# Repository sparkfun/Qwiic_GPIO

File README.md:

SparkFun Qwiic GPIO
=======================================

[*SparkFun Qwiic GPIO (DEV-17047)*](https://www.sparkfun.com/products/17047)

TCA9534 breakout board with Qwiic connectors and easy-to-use latch terminals; no longer screw wires into place! Use this board to add more GPIO pins to your system.

Repository Contents
-------------------

* **/Documents** - Contains datasheets and schematic.pdf
* **/Hardware** - Current .brd and .sch files for product
* **/Production** - Production panel files (.brd)

License Information
-------------------

This product is _**open source**_!

Please review the LICENSE.md file for license information.

If you have any questions or concerns on licensing, please contact technical support on our [SparkFun forums](https://forum.sparkfun.com/viewforum.php?f=152).

Distributed as-is; no warranty is given.

- Your friends at SparkFun._

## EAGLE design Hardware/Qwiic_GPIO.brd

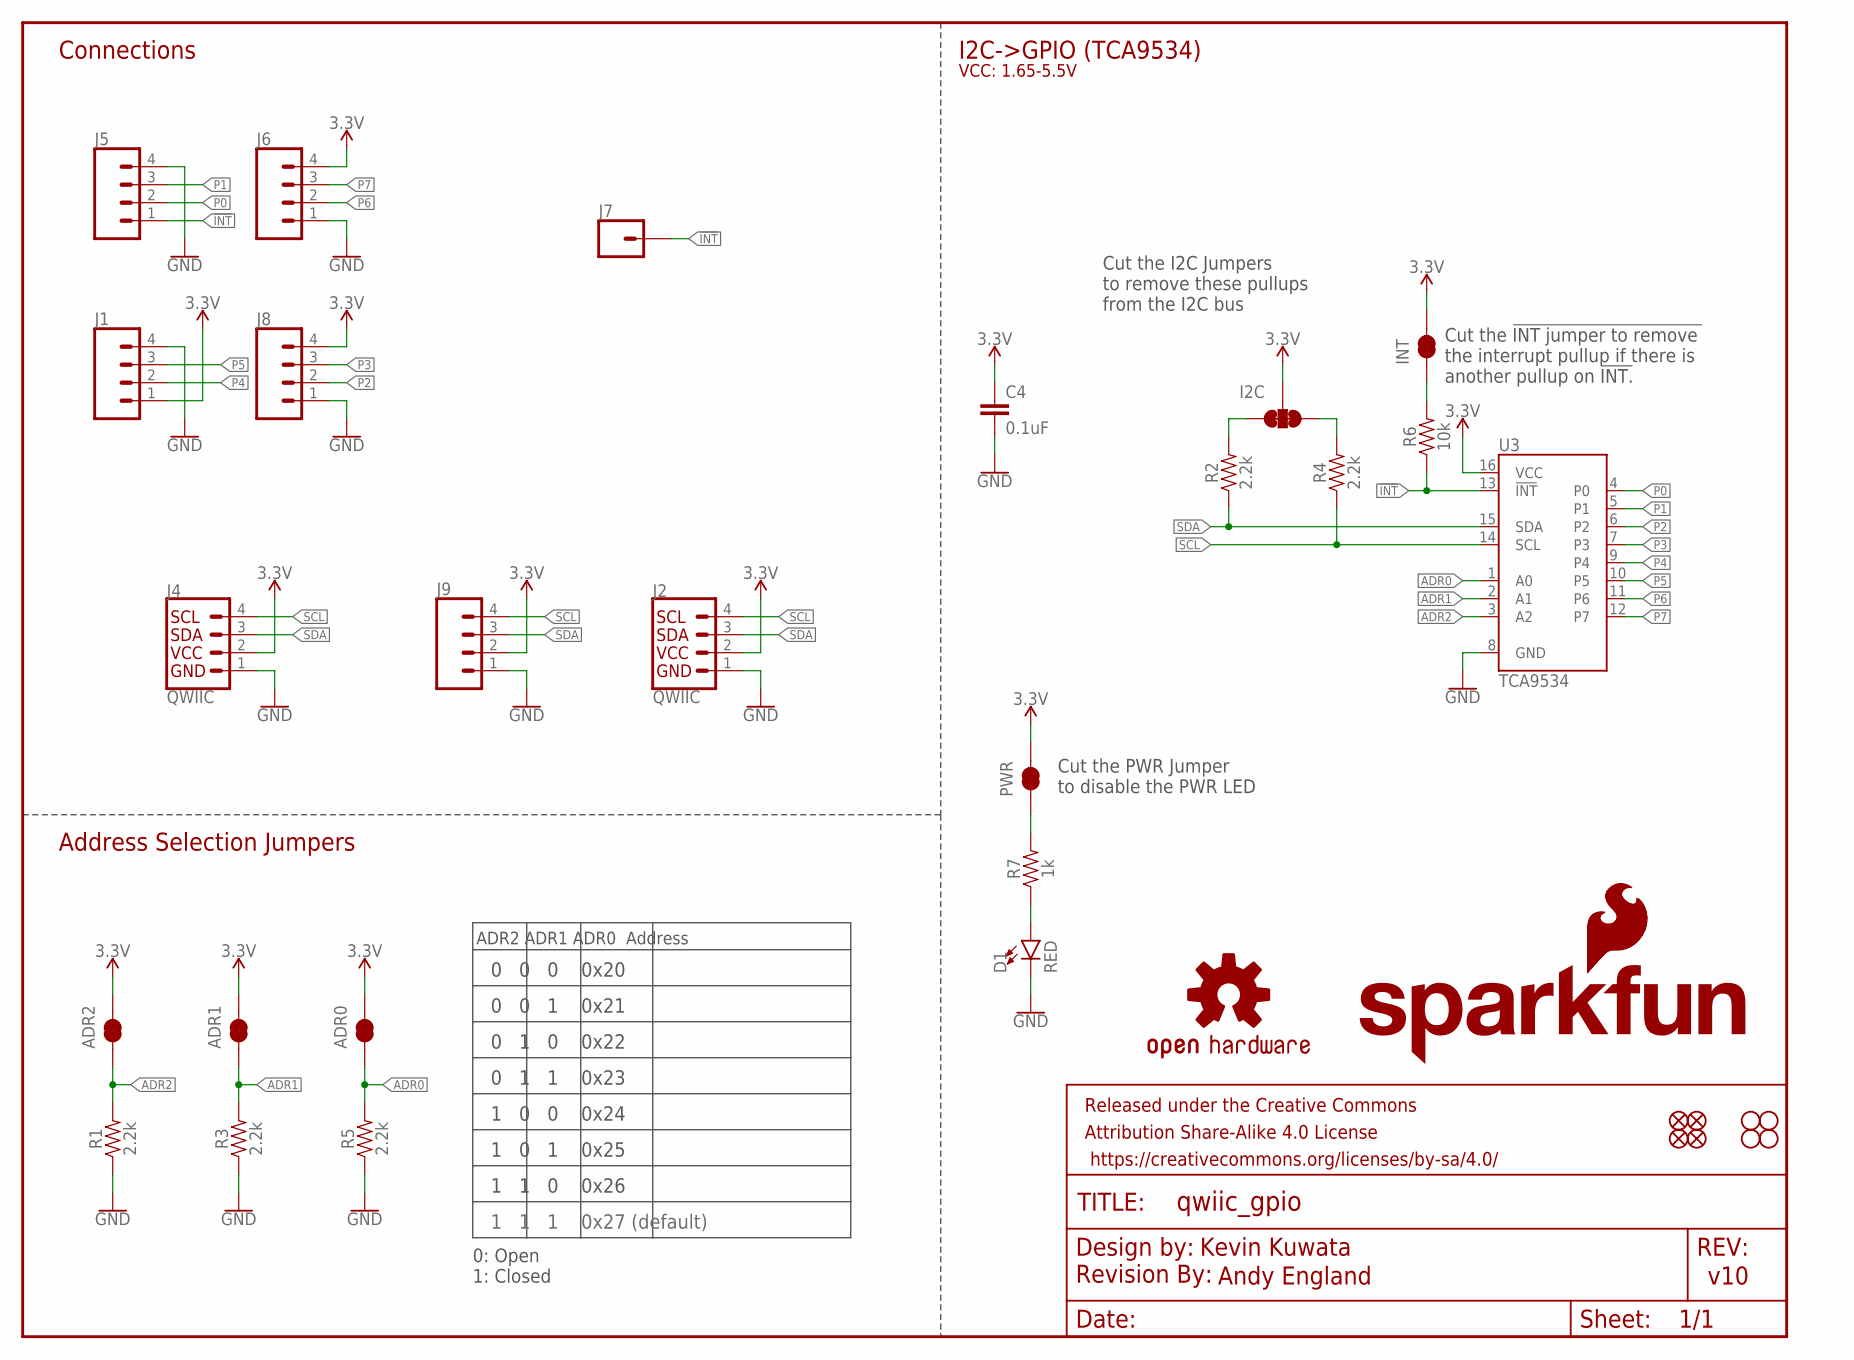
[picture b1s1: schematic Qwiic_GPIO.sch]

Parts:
ADR0, ADR1, ADR2: JUMPER-SMT_2_NC_TRACE_SILK; SMT-JUMPER_2_NC_TRACE_SILK
C4: 0.1uF; 0603
D1: RED; LED-0603
FD1, FD2: FIDUCIAL1X2; FIDUCIAL-1X2
FRAME1: FRAME-LETTER; CREATIVE_COMMONS
H1, H2: STAND-OFF
I2C: JUMPER-SMT_3_2-NC_TRACE_SILK; SMT-JUMPER_3_2-NC_TRACE_SILK
INT: JUMPER-SMT_2_NC_TRACE_SILK; SMT-JUMPER_2_NC_TRACE_SILK
J1, J5, J6, J8: CONN_04LATCH; LATCHTERMINAL-5MM-4
J2, J4: QWIIC; JST04_1MM_RA
J7: CONN_01PTH_NO_SILK_YES_STOP; 1X01_NO_SILK
J9: CONN_041X04_NO_SILK; 1X04_NO_SILK
JP2, JP6: FIDUCIAL1X2; FIDUCIAL-1X2
JP3, JP4: STAND-OFF
LOGO1: OSHW-LOGOMINI; OSHW-LOGO-MINI
LOGO2: REVISION
LOGO3: SFE_LOGO_NAME_FLAME.1_INCH; SFE_LOGO_NAME_FLAME_.1
LOGO4: SFE_LOGO_FLAME.2_INCH; SFE_LOGO_FLAME_.2
PWR: JUMPER-SMT_2_NC_TRACE_SILK; SMT-JUMPER_2_NC_TRACE_SILK
R1, R2, R3, R4, R5: 2.2k; 0603
R6: 10k; 0603
R7: 1k; 0603
U3: TCA9534; 16SOIC

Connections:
3.3V: ADR0.2, ADR1.2, ADR2.2, C4.1, I2C.2, INT.2, J1.1, J2.2, J4.2, J6.4, J8.4, J9.2, PWR.2, U3.16 (VCC)
!INT: J5.1, J7.1, R6.1, U3.13 (!INT)
ADR0: ADR0.1, R5.2, U3.1 (A0)
ADR1: ADR1.1, R3.2, U3.2 (A1)
ADR2: ADR2.1, R1.2, U3.3 (A2)
GND: C4.2, D1.C, J1.4, J2.1, J4.1, J5.4, J6.1, J8.1, J9.1, R1.1, R3.1, R5.1, U3.8 (GND)
unnamed: INT.1, R6.2
unnamed: D1.A, R7.1
unnamed: PWR.1, R7.2
P0: J5.2, U3.4 (P0)
P1: J5.3, U3.5 (P1)
P2: J8.2, U3.6 (P2)
P3: J8.3, U3.7 (P3)
P4: J1.2, U3.9 (P4)
P5: J1.3, U3.10 (P5)
P6: J6.2, U3.11 (P6)
P7: J6.3, U3.12 (P7)
SCL: J2.4, J4.4, J9.4, R4.1, U3.14 (SCL)
SCL_PU1: I2C.1, R2.2
SDA: J2.3, J4.3, J9.3, R2.1, U3.15 (SDA)
SDA_PU1: I2C.3, R4.2

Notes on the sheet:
Kevin Kuwata
v10
Address Selection Jumpers
ADR2 ADR1 ADR0 Address
0 0 0 0x20
0 0 1 0x21
0 1 0 0x22
0 1 1 0x23
1 0 0 0x24
1 0 1 0x25
1 1 0 0x26
1 1 1 0x27 (default)
0: Open 1: Closed
I2C->GPIO (TCA9534)
Connections
VCC: 1.65-5.5V
Andy England
Cut the !INT jumper to remove the interrupt pullup if there is another pullup on !INT.
Cut the I2C Jumpers to remove these pullups from the I2C bus
Cut the PWR Jumper to disable the PWR LED

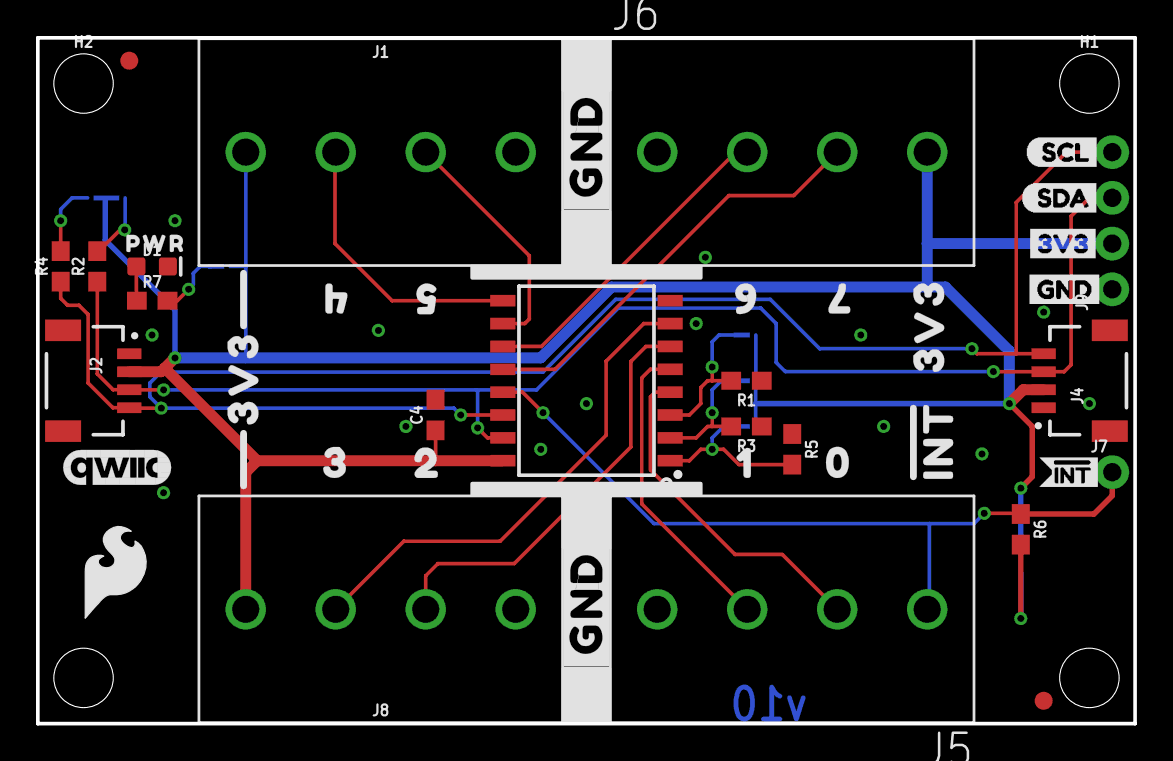
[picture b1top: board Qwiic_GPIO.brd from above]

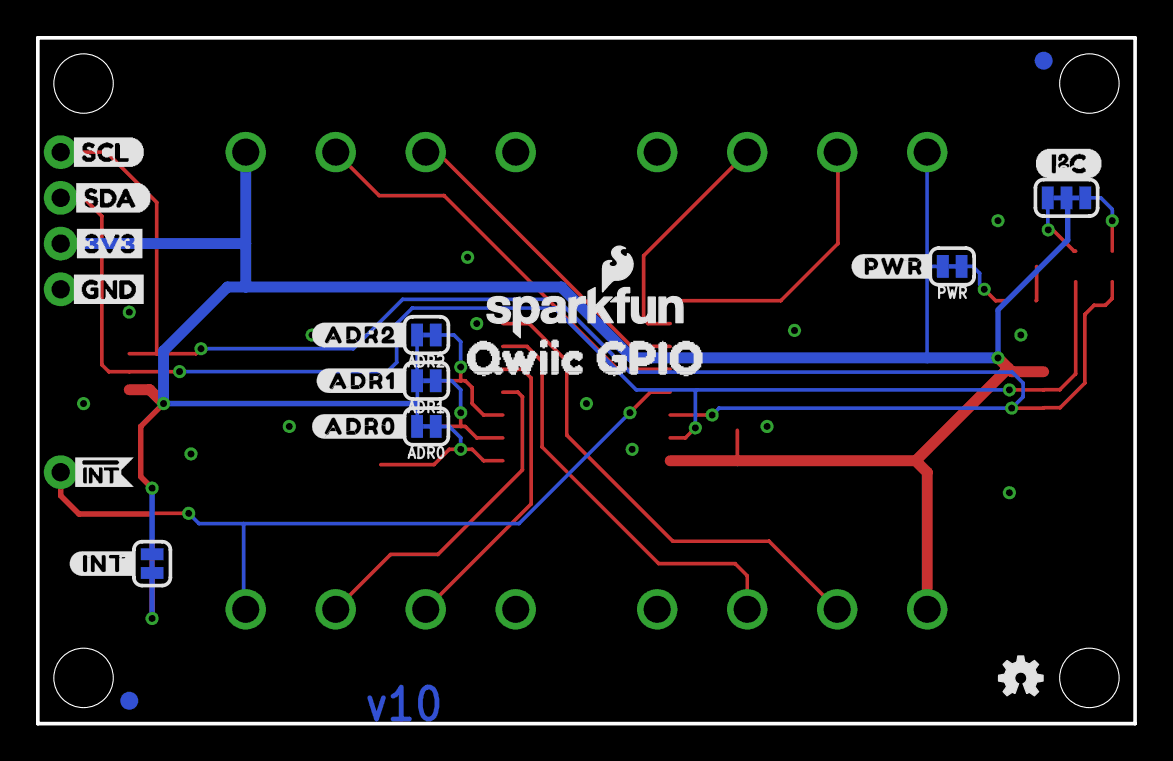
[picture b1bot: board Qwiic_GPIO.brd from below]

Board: 2 copper layers, 61.0 x 38.1 mm, 69 parts (22 on the bottom side), 21 nets.

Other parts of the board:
U$1: I2C
U$2: 20
U$3, U$26: 3V33
U$4: 30
U$5: #ADR1#0
U$6: 10
U$7, U$25: GND4
U$8: QWIIC_GPIO7
U$9: SCL6
U$10: SDA5
U$11: #ADR2#0
U$12: #INT#0
U$13, U$22, U$29: #INT0
U$14: 00
U$15: #ADR0#0
U$21: QWIIC_6MM
U$23: SCL0
U$24: SDA1
U$30, U$31: 3V30
U$32: 40
U$33: 50
U$34: PWR0
U$35: 60
U$37: 70
U$38, U$40: #GND#0
U$39: #PWR#0

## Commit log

2020-08-06 Updating address jumper note
2020-08-10 adding rest of GPIO pins
2020-08-20 post checklist changes
2020-08-20 removing libraries
2020-08-20 moving text on schematic
2020-08-24 uploading panel
2020-08-27 pushing panel
2020-10-08 Update README
    Update for release.
2020-10-08 Cleanup
    Cleaning up old files for release.
2020-11-20 Update README.md
    Added missing links
2020-11-20 Create License.md
    Added license

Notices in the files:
parts and their libraries:
SparkFun-Resistors: Licensing: Creative Commons ShareAlike 4.0 International - https://creativecommons.org/licenses/by-sa/4.0
SparkFun-Aesthetics: Released under the Creative Commons Attribution Share-Alike 4.0 License
SparkFun-Aesthetics: https://creativecommons.org/licenses/by-sa/4.0
